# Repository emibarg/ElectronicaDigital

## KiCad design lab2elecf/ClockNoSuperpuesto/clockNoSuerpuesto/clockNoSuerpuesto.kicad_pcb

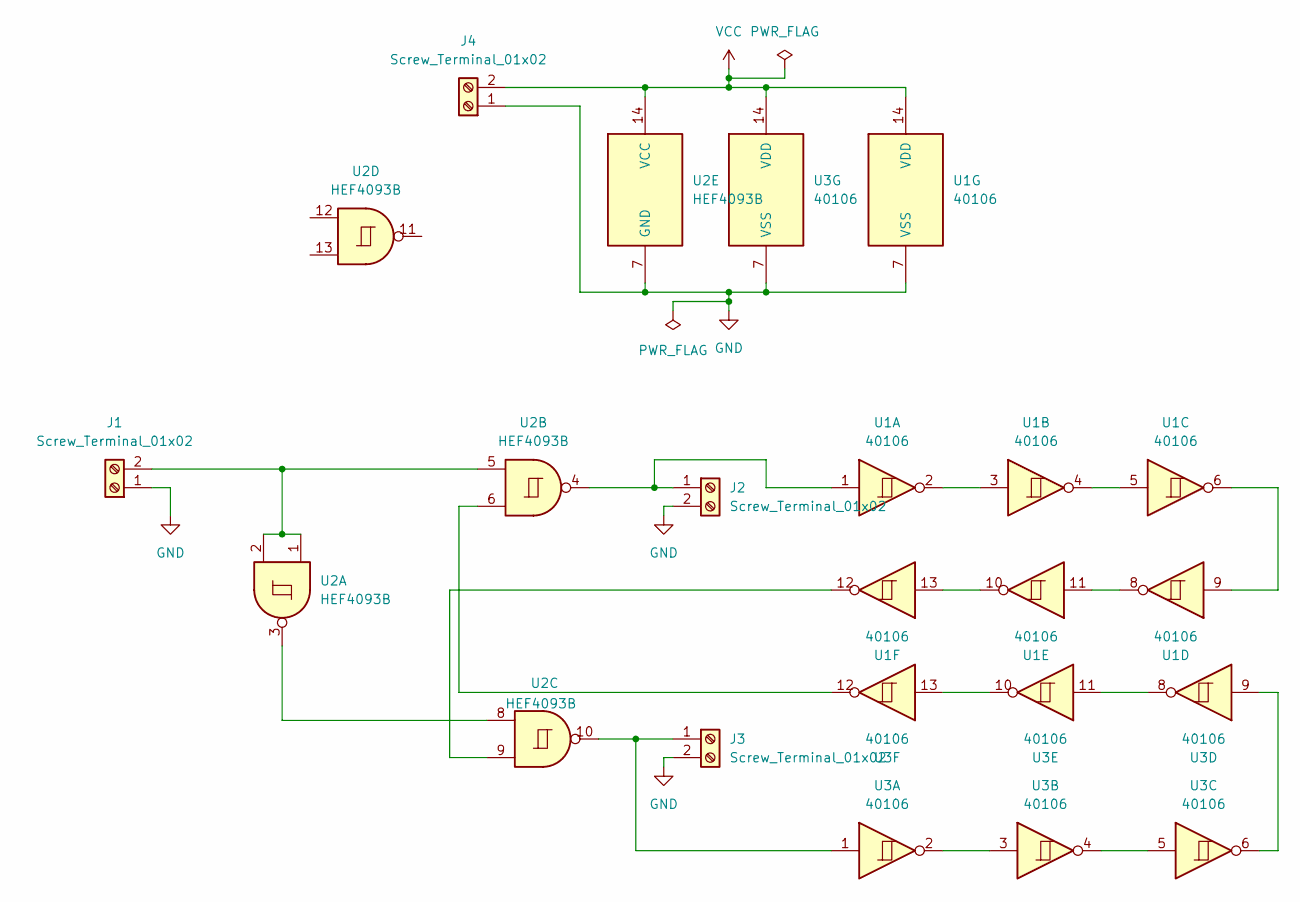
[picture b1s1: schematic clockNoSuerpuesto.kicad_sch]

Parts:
J1, J2, J3, J4: Screw_Terminal_01x02; TerminalBlock_bornier-2_P5.08mm
U1, U3: 40106; DIP-14_W7.62mm_Socket_LongPads
U2: HEF4093B; DIP-14_W7.62mm_Socket_LongPads

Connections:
GND: J1.1, J2.2, J3.2, J4.1, U1.7 (VSS), U2.7 (GND), U3.7 (VSS)
unnamed: J1.2, U2.1, U2.2, U2.5
unnamed: J2.1, U1.1, U2.4
unnamed: J3.1, U2.10, U3.1
unnamed: U1.2, U1.3
unnamed: U1.4, U1.5
unnamed: U1.6, U1.9
unnamed: U1.10, U1.13
unnamed: U1.8, U1.11
unnamed: U1.12, U2.9
unnamed: U2.3, U2.8
unnamed: U2.6, U3.12
unnamed: U3.2, U3.3
unnamed: U3.4, U3.5
unnamed: U3.6, U3.9
unnamed: U3.10, U3.13
unnamed: U3.8, U3.11
VCC: J4.2, U1.14 (VDD), U2.14 (VCC), U3.14 (VDD)

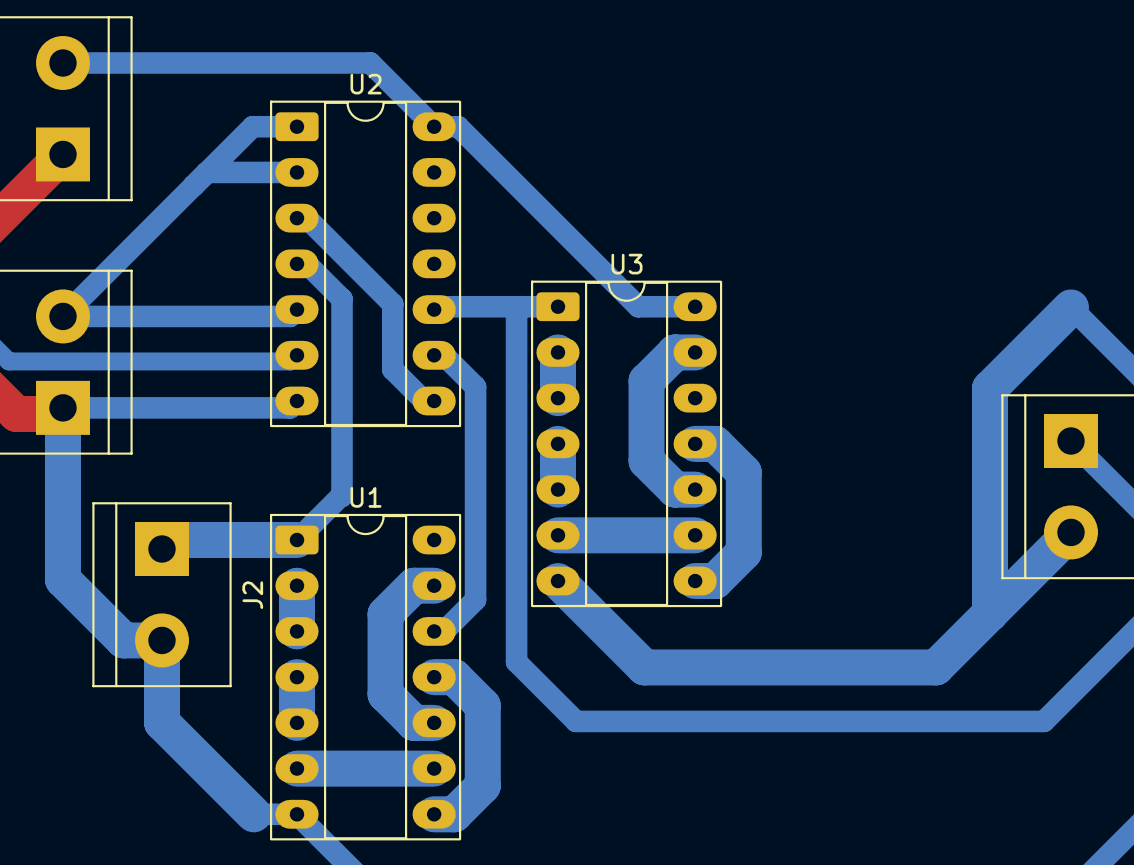
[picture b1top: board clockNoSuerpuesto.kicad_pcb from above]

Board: 2 copper layers, 7 parts (0 on the bottom side), 18 nets.

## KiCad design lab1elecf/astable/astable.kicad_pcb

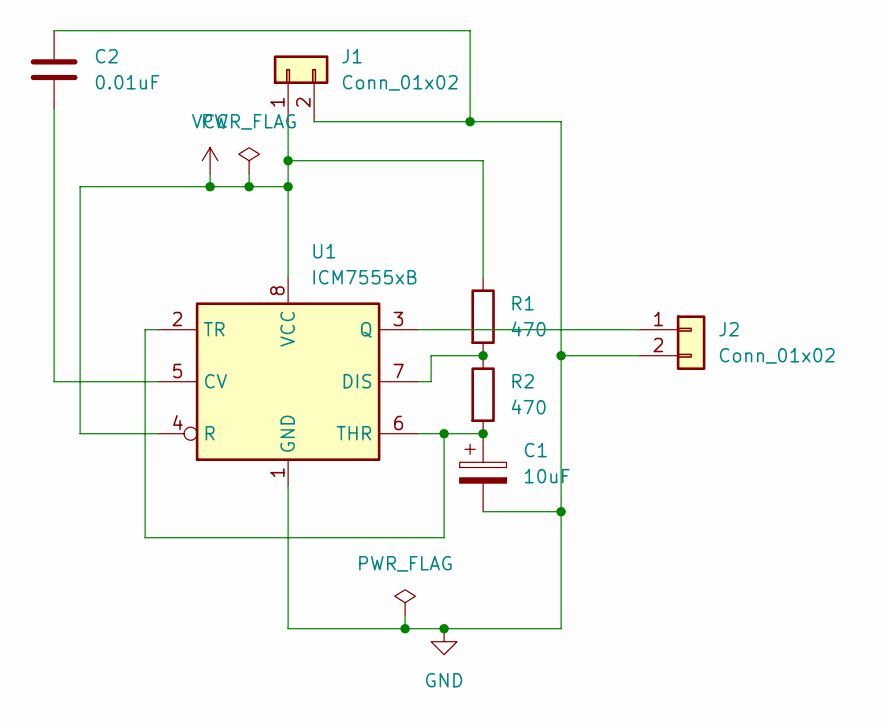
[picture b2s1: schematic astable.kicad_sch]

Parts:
C1: 10uF; CP_Radial_D5.0mm_P2.50mm
C2: 0.01uF; C_Disc_D4.3mm_W1.9mm_P5.00mm
J1, J2: Conn_01x02; TerminalBlock_bornier-2_P5.08mm
R1, R2: 470; R_Axial_DIN0204_L3.6mm_D1.6mm_P7.62mm_Horizontal
U1: ICM7555xB; DIP-8_W7.62mm_Socket

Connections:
GND: C1.2, C2.1, J1.2, J2.2, U1.1 (GND)
unnamed: J2.1, U1.3 (Q)
unnamed: C2.2, U1.5 (CV)
unnamed: R1.2, R2.1, U1.7 (DIS)
unnamed: C1.1, R2.2, U1.2 (TR), U1.6 (THR)
VCC: J1.1, R1.1, U1.4 (R), U1.8 (VCC)

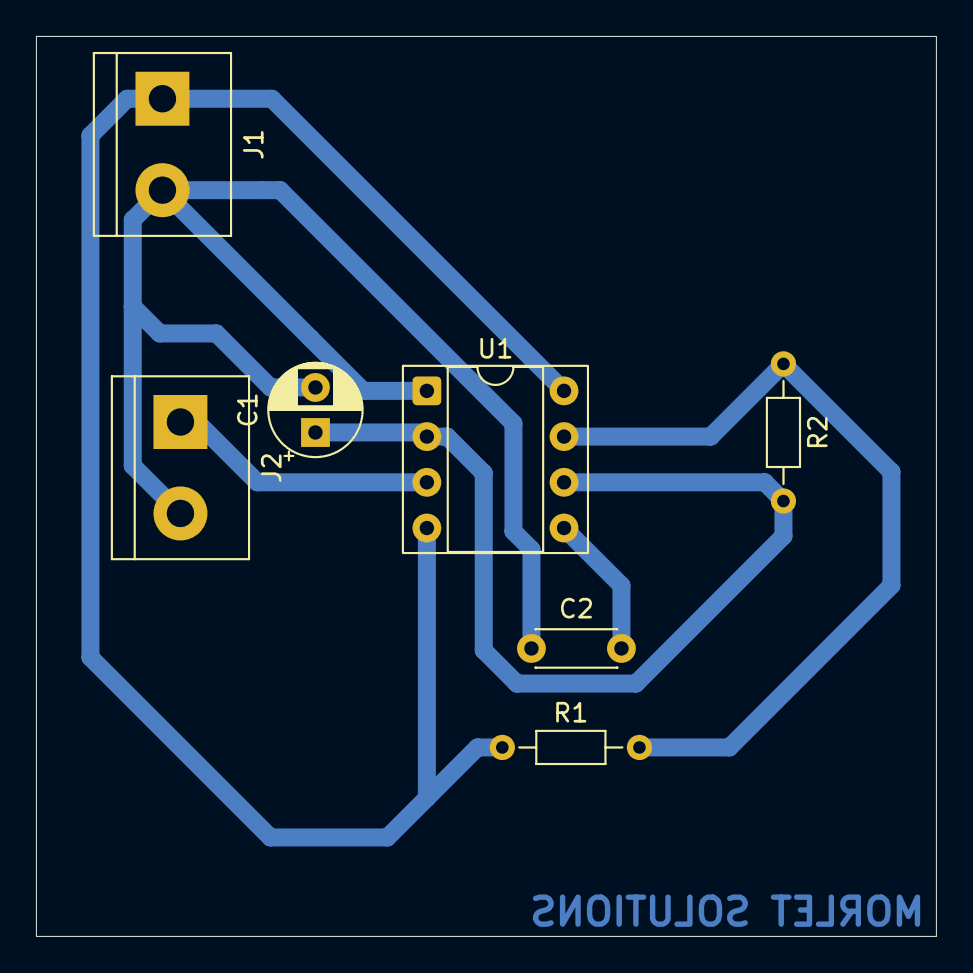
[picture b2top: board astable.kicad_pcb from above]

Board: 2 copper layers, 50.0 x 50.0 mm, 7 parts (0 on the bottom side), 6 nets.

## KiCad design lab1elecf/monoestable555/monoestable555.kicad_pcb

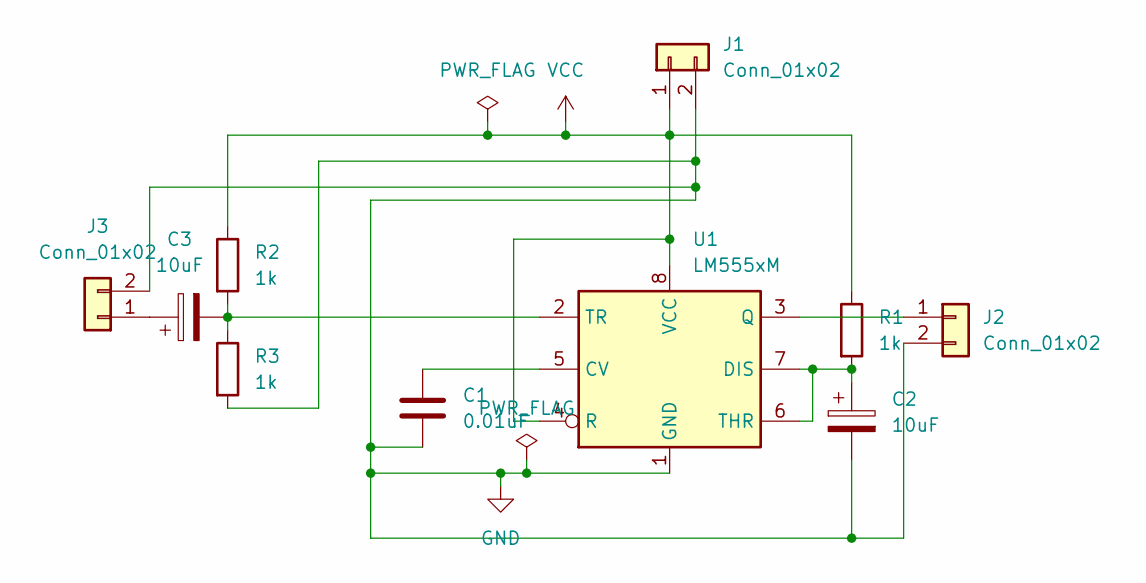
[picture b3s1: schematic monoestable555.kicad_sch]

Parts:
C1: 0.01uF; C_Disc_D4.3mm_W1.9mm_P5.00mm
C2, C3: 10uF; CP_Radial_D5.0mm_P2.00mm
J1, J2, J3: Conn_01x02; TerminalBlock_bornier-2_P5.08mm
R1, R2, R3: 1k; R_Axial_DIN0204_L3.6mm_D1.6mm_P7.62mm_Horizontal
U1: LM555xM; DIP-8_W7.62mm_Socket

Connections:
GND: C1.2, C2.2, J1.2, J2.2, J3.2, R3.2, U1.1 (GND)
unnamed: J2.1, U1.3 (Q)
unnamed: C3.1, J3.1
unnamed: C1.1, U1.5 (CV)
unnamed: C2.1, R1.2, U1.6 (THR), U1.7 (DIS)
unnamed: C3.2, R2.2, R3.1, U1.2 (TR)
VCC: J1.1, R1.1, R2.1, U1.4 (R), U1.8 (VCC)

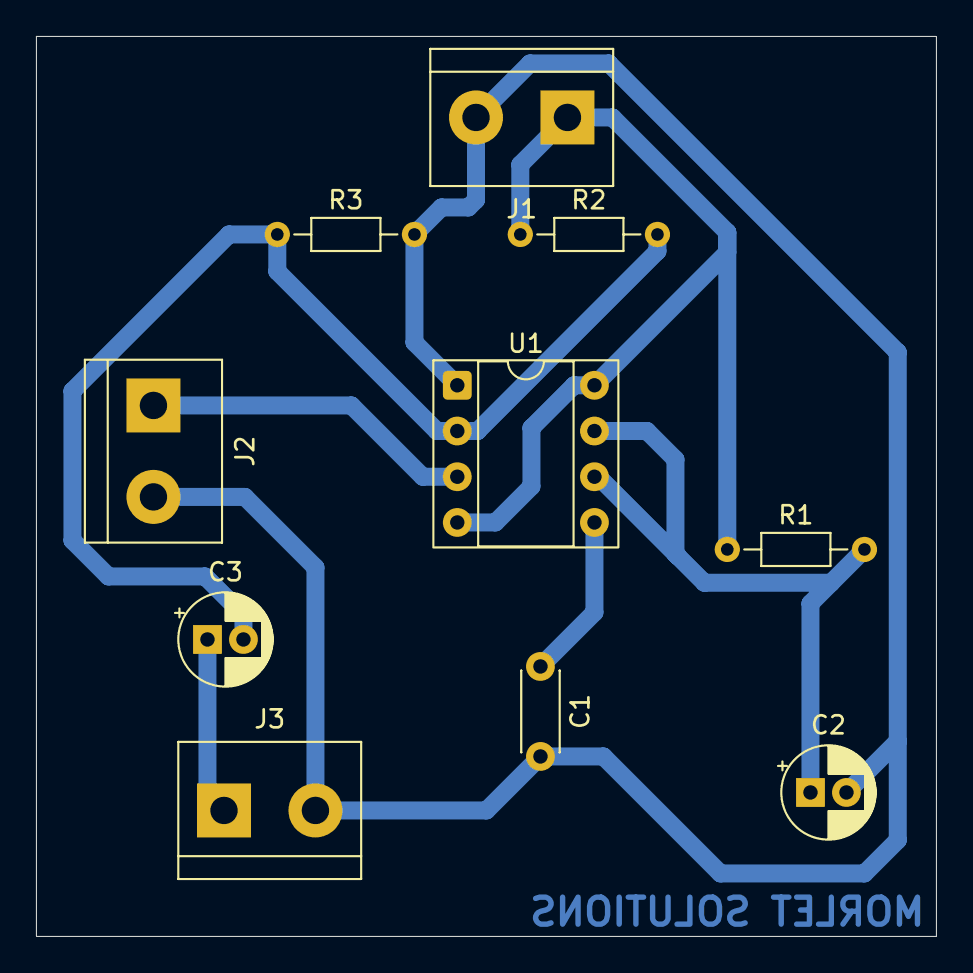
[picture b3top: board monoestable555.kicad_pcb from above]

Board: 2 copper layers, 50.0 x 50.0 mm, 10 parts (0 on the bottom side), 7 nets.

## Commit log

2025-03-22 monoestableCMOS
2025-03-22 mono555
2025-03-22 added morlet
2025-03-24 VCC Y GND
2025-03-26 monoCMOS nefasto
2025-04-05 lab 2 innit
2025-04-05 foto de proto del CNS
